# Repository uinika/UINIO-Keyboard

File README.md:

# UINIO-Keyboard 多功能输入模组

[**UINIO-Keyboard**](https://gitee.com/uinika/UINIO-Keyboard) 是一款基于[**江苏沁恒 CH452**](https://www.wch.cn/products/CH452.html) 的 64 位键盘输入装置，采用两线制的 **I²C** 总线通信接口，并且外扩有[**日本阿尔卑斯阿尔派（ALPSALPINE）**](https://www.alpsalpine.com/) 的 3 枚 **EC11** 旋转编码器、以及 1 枚 **RKJXV** 模拟量碳膜摇杆，基本覆盖了嵌入式开发当中主流的实体输入方案。

## 设计概要

1. 同时板载有 **编码键盘**、**旋转编码器**、**模拟量摇杆** 三种常用的输入外设；
2. 添加了六枚 `3mm` 直径的机械孔，便于使用**铜柱**或者**螺丝**进行固定和安装；
3. 键盘按键使用 `3 × 4 × 2.5` 封装规格的四引脚贴片按键，这里可以购买日本[**阿尔卑斯阿尔派**](https://www.alpsalpine.com/c/)的 `SKRPACE010` 型，或者国产[**讯普精密**](https://www.xunpu.com.cn/)的 `TS-1089S-02526` 型微动按键；
4. 碳膜摇杆如果购买不到日本**阿尔卑斯阿尔派**（ALPS Alpine）的原厂型号，那么可以平替为国产的 [**广东控银 JP13**](http://www.k-silver.com/c_html_products/jp13heisedaikaiguan-825.html) 型摇杆；
5. 关于 64 位键盘的具体键位编码，以及参考驱动程序，可以查阅沁恒官方的[**《数码管驱动及键盘控制芯片 CH452 数据手册》**](https://www.wch.cn/downloads/CH452DS1_PDF.html)；

## 参考技术文档

[UinIO.com 电子技术实验室](http://uinio.com/) 为 **UINIO-Keyboard** 开源项目提供了如下参考技术资料：

- [《UINIO-Keyboard 核心板原理图》](http://uinio.com/my/works/UINIO-Keyboard/UINIO-Keyboard-Schematic.pdf)
- [《交互式 BOM 物料清单与 PCB 版图在线预览》](http://uinio.com/my/works/UINIO-Keyboard/UINIO-Keyboard-BOM.html)

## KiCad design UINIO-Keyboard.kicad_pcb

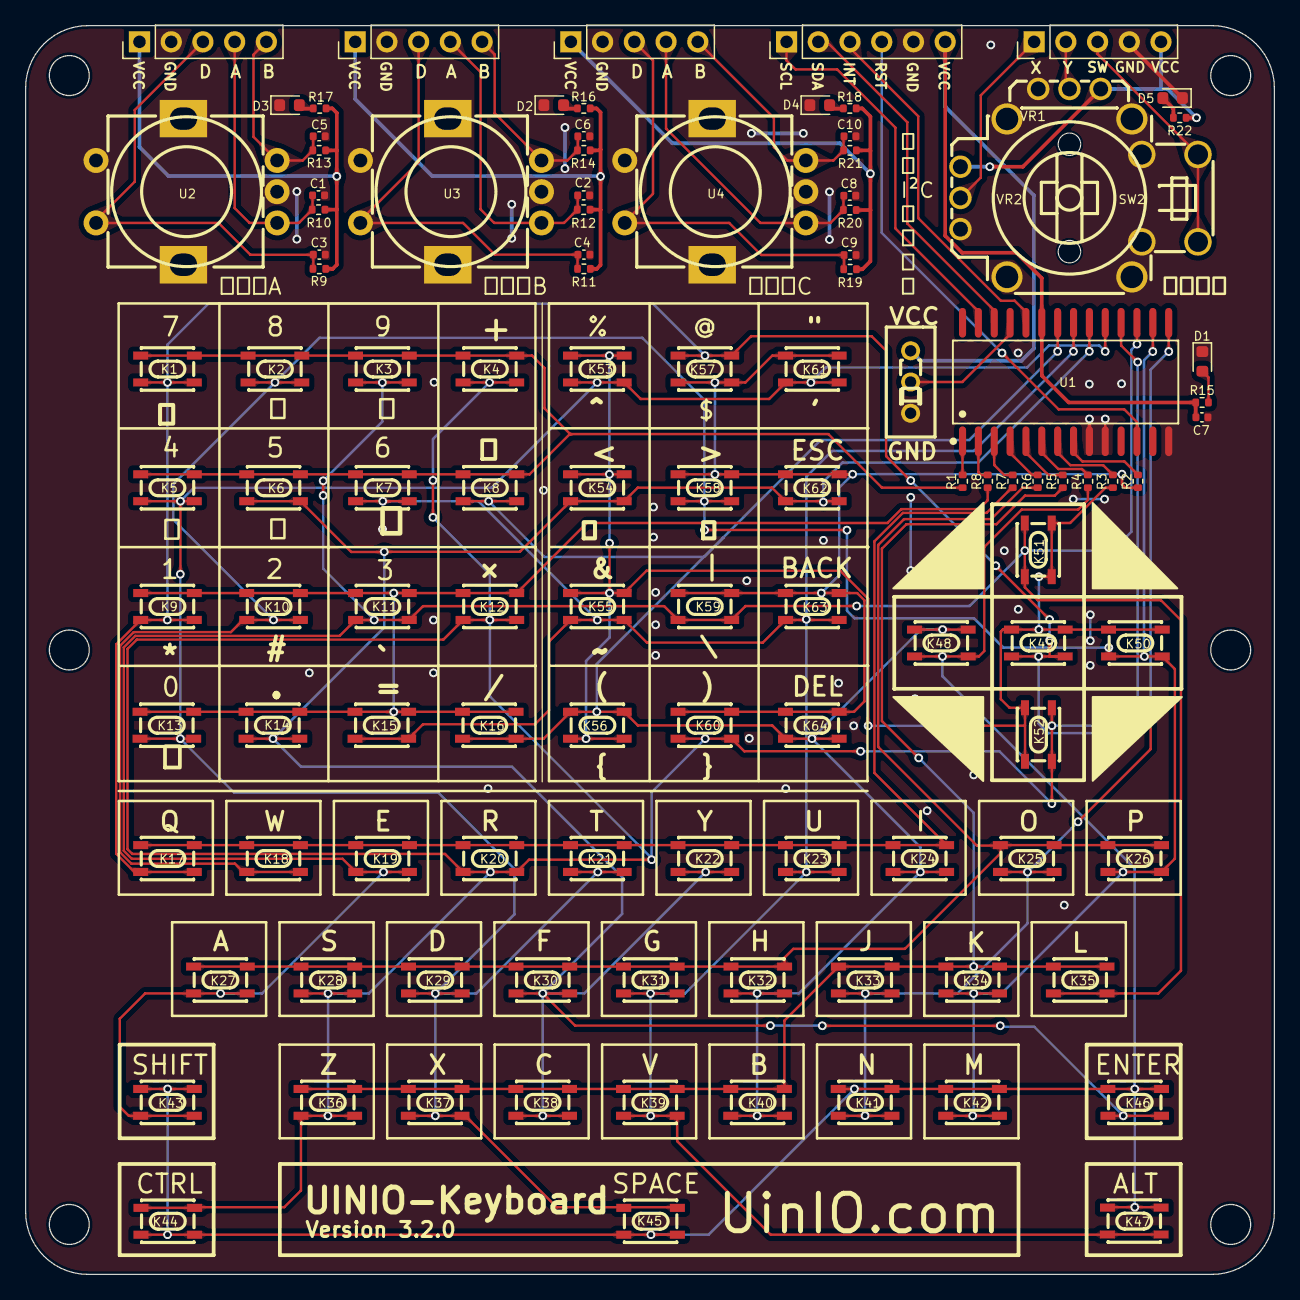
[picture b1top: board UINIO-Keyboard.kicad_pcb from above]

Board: 2 copper layers, 100.0 x 100.0 mm, 112 parts (0 on the bottom side), 52 nets.

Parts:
C1, C2, C5, C6, C8, C10: 0.01uF; C_0402_1005Metric
C3, C4, C7, C9: 0.1uF; C_0402_1005Metric
D1, D2, D3, D4, D5: LED_Red; LED_0603_1608Metric
J1: Conn_01x06_Pin; PinHeader_1x06_P2.54mm_Vertical
J2, J3, J4, J5: Conn_01x05_Pin; PinHeader_1x05_P2.54mm_Vertical
K1, K2, K3, K4, K5, K6, K7, K8, K9, K10, K11, K12, K13, K14, K15, K16, K17, K18, K19, K20, K21, K22, K23, K24, K25, K26, K27, K28, K29, K30, K31, K32, K33, K34, K35, K36, K37, K38, K39, K40, K41, K42, K43, K44, K45, K46, K47, K48, K49, K50, K51, K52, K53, K54, K55, K56, K57, K58, K59, K60, K61, K62, K63, K64: A; KEY-SMD_4P-L4.2-W3.4-P2.15-LS4.7
R1, R2, R3, R4, R5, R6, R7, R8, R9, R10, R11, R12, R13, R14, R19, R20, R21: 10K; R_0402_1005Metric
R15, R16, R17, R18, R22: 2K; R_0402_1005Metric
SW1: SWITCH_SS12D00G3; SW-TH_SS-12D01-GX
SW2: RKJXV1224005; SW-TH_RKJXV1224005
U1: CH452A; SOIC-28_L17.9-W7.5-P1.27-LS10.3-BL
U2, U3, U4: EC1106S; SW-TH_EC11S

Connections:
/DCLK: J1.1, U1.27 (DCLK)
/DIG0: R1.1, U1.8 (DIG0)
/DIG1: R2.1, U1.7 (DIG1)
/DIG2: R3.1, U1.6 (DIG2)
/DIG3: R4.1, U1.5 (DIG3)
/DIG4: R5.1, U1.4 (DIG4)
/DIG5: R6.1, U1.3 (DIG5)
/DIG6: R7.1, U1.2 (DIG6)
/DIG7: R8.1, U1.1 (DIG7)
/DIN: J1.2, U1.26 (DIN)
/DOUT: J1.3, U1.24 (DOUT)
/EC11-A-1: C1.1, J2.4, R10.1, U2.1 (A)
/EC11-A-2: C2.1, J3.4, R12.1, U3.1 (A)
/EC11-A-3: C8.1, J5.4, R20.1, U4.1 (A)
/EC11-B-1: C5.1, J2.5, R13.1, U2.3 (B)
/EC11-B-2: C6.1, J3.5, R14.1, U3.3 (B)
/EC11-B-3: C10.1, J5.5, R21.1, U4.3 (B)
/EC11-D-1: C3.1, J2.3, R9.1, U2.5 (D)
/EC11-D-2: C4.1, J3.3, R11.1, U3.5 (D)
/EC11-D-3: C9.1, J5.3, R19.1, U4.5 (D)
/EC11-VCC-1: J2.1, R9.2, R10.2, R13.2, R17.2
/EC11-VCC-2: J3.1, R11.2, R12.2, R14.2, R16.2
/EC11-VCC-3: J5.1, R18.2, R19.2, R20.2, R21.2
/LOAD: SW1.2, U1.25 (LOAD)
/RST: J1.4, U1.12 (RST)
/Rocker_SW: J4.3, SW2.b, SW2.d
/Rocker_VCC: J4.5, R22.2, SW2.1 (B), SW2.4 (A)
/Rocker_X: J4.1, SW2.5 (DTA)
/Rocker_Y: J4.2, SW2.2 (DTA)
/SEG0: K1.3, K1.4, K9.3, K9.4, K17.3, K17.4, K25.3, K25.4, K33.3, K33.4, K41.3, K41.4, K49.3, K49.4, K57.3, K57.4, U1.15 (SEG0)
/SEG1: K2.3, K2.4, K10.3, K10.4, K18.3, K18.4, K26.3, K26.4, K34.3, K34.4, K42.3, K42.4, K50.3, K50.4, K58.3, K58.4, U1.16 (SEG1)
/SEG2: K3.3, K3.4, K11.3, K11.4, K19.3, K19.4, K27.3, K27.4, K35.3, K35.4, K43.3, K43.4, K51.3, K51.4, K59.3, K59.4, U1.17 (SEG2)
/SEG3: K4.3, K4.4, K12.3, K12.4, K20.3, K20.4, K28.3, K28.4, K36.3, K36.4, K44.3, K44.4, K52.3, K52.4, K60.3, K60.4, U1.18 (SEG3)
/SEG4: K5.3, K5.4, K13.3, K13.4, K21.3, K21.4, K29.3, K29.4, K37.3, K37.4, K45.3, K45.4, K53.3, K53.4, K61.3, K61.4, U1.19 (SEG4)
/SEG5: K6.3, K6.4, K14.3, K14.4, K22.3, K22.4, K30.3, K30.4, K38.3, K38.4, K46.3, K46.4, K54.3, K54.4, K62.3, K62.4, U1.20 (SEG5)
/SEG6: K7.3, K7.4, K15.3, K15.4, K23.3, K23.4, K31.3, K31.4, K39.3, K39.4, K47.3, K47.4, K55.3, K55.4, K63.3, K63.4, U1.21 (SEG6)
/SEG7: K8.3, K8.4, K16.3, K16.4, K24.3, K24.4, K32.3, K32.4, K40.3, K40.4, K48.3, K48.4, K56.3, K56.4, K64.3, K64.4, U1.22 (SEG7)
/VCC: C7.1, J1.6, R15.2, SW1.3, U1.23 (VCC)
GND: C1.2, C2.2, C3.2, C4.2, C5.2, C6.2, C7.2, C8.2, C9.2, C10.2, D1.1 (K), D2.1 (K), D3.1 (K), D4.1 (K), D5.1 (K), J1.5, J2.2, J3.2, J4.4, J5.2, SW1.1, SW2.3 (A), SW2.6 (B), SW2.7 (GND), SW2.8 (GND), SW2.9 (GND), SW2.10 (GND), SW2.a, SW2.c, U1.9 (GND), U1.10 (GND), U1.14 (H3L2), U2.2 (C), U2.4 (E), U2.6 (EP), U2.7 (EP), U3.2 (C), U3.4 (E), U3.6 (EP), U3.7 (EP), U4.2 (C), U4.4 (E), U4.6 (EP), U4.7 (EP)
unnamed: D1.2 (A), R15.1
unnamed: D2.2 (A), R16.1
unnamed: D3.2 (A), R17.1
unnamed: D4.2 (A), R18.1
unnamed: D5.2 (A), R22.1
unnamed: K1.1, K1.2, K2.1, K2.2, K3.1, K3.2, K4.1, K4.2, K5.1, K5.2, K6.1, K6.2, K7.1, K7.2, K8.1, K8.2, R8.2
unnamed: K9.1, K9.2, K10.1, K10.2, K11.1, K11.2, K12.1, K12.2, K13.1, K13.2, K14.1, K14.2, K15.1, K15.2, K16.1, K16.2, R7.2
unnamed: K17.1, K17.2, K18.1, K18.2, K19.1, K19.2, K20.1, K20.2, K21.1, K21.2, K22.1, K22.2, K23.1, K23.2, K24.1, K24.2, R6.2
unnamed: K25.1, K25.2, K26.1, K26.2, K27.1, K27.2, K28.1, K28.2, K29.1, K29.2, K30.1, K30.2, K31.1, K31.2, K32.1, K32.2, R5.2
unnamed: K33.1, K33.2, K34.1, K34.2, K35.1, K35.2, K36.1, K36.2, K37.1, K37.2, K38.1, K38.2, K39.1, K39.2, K40.1, K40.2, R4.2
unnamed: K41.1, K41.2, K42.1, K42.2, K43.1, K43.2, K44.1, K44.2, K45.1, K45.2, K46.1, K46.2, K47.1, K47.2, K48.1, K48.2, R3.2
unnamed: K49.1, K49.2, K50.1, K50.2, K51.1, K51.2, K52.1, K52.2, K53.1, K53.2, K54.1, K54.2, K55.1, K55.2, K56.1, K56.2, R2.2
unnamed: K57.1, K57.2, K58.1, K58.2, K59.1, K59.2, K60.1, K60.2, K61.1, K61.2, K62.1, K62.2, K63.1, K63.2, K64.1, K64.2, R1.2

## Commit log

2023-03-10 Initialize the project.
2023-03-13 Update PCB
2023-03-14 Update PCB.
2023-05-17 Complete schematic drawing.
2023-05-18 PCB Layout.
2023-05-20 Update PCB Layout.
2023-05-22 Complete PCB layout.
2023-05-22 Update documents.
2023-05-24 Finish PCB layout.
2023-05-25 Release UINIO-Keyboard version 1.0.0.
2023-05-29 Prepare version 2.0.0.
2023-06-25 Release UINIO-Keyboard version 2.0.0.
2023-06-27 Prepare 3.0.0.
2023-06-27 Release UINIO-Keyboard version 3.0.0.
2023-06-27 Prepare version 3.0.0.
2023-06-29 Release UINIO-Keyboard veresion 3.0.0.
2023-07-09 Release UINIO-Keyboard version 3.1.0.
2023-07-11 Update README.md.
2024-01-11 Release UINIO-Keyboard version 3.1.1.
2024-11-29 Release UINIO-Keyboard version 3.2.0.
